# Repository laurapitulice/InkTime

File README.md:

# ⌚ "InkTime smartwatch" - PCB layout in Autodesk Fusion360
InkTime is an e-paper smartwatch designed for month-class battery life, sunlight-readable time-first UX, and essential phone notifications with basic activity
tracking.
Developed in Autodesk Fusion 360, the PCB layout adheres to the precise dimensions and mounting requirements of the wearable chassis, ensuring a seamless fit and optimal component placement.

---

## Hardware Diagram

This is an open-hardware wearable based on the nRF52840 microcontroller.

---

## System Architecture

### 1. Microcontroller (MCU)
- **Chip:** Nordic nRF52840 (Cortex-M4F @ 64MHz)
- **Memory:** 1MB Flash, 256KB RAM
- **Radio:** Bluetooth 5.4 Low Energy with integrated ceramic antenna
- **Oscillators:** 32MHz (operational) and 32.768kHz (sleep mode/RTC)

### 2. Power Management
- **Li-Po Charger:** BQ25180 (I2C control, programmable current)
- **Voltage Regulator:** RT6100 Buck-Boost (stable 3.3V output)
- **Battery Monitoring:** MAX17048 Fuel Gauge (ModelGauge algorithm)
- **Charging Interface:** USB-C with USBLC6-2 ESD protection

### 3. Display (E-Paper)
- **Type:** Electronic Paper Display (EPD)
- **Interface:** SPI + Power Gating Control (PWR_EPD)
- **Drive Circuit:** On-board integrated Boost converter (MBR0530 Diodes, L5 10uH) for VGH/VGL generation

### 4. Sensors and Feedback
- **IMU:** BMA421 (Ultra-low power accelerometer connected via I2C)
- **Haptic:** DRV2605 (Vibration driver with integrated effects library via I2C)
- **Input:** 3 mechanical buttons (UP, ENTER, DOWN) with filtering circuits

### 5. Communication Interfaces (I2C Mapping)
| Component | Function | Interface |
| :--- | :--- | :--- |
| **BMA421** | Motion Sensor | I2C |
| **MAX17048** | Battery Status | I2C |
| **DRV2605** | Vibration Motor | I2C |
| **BQ25180** | Charging | I2C |

---

## nRF52840 Pin Mapping

| Pin nRF52840 | Signal      | Component | Interface |
|-------------|------------|------------|----------|
| P0.00/XL1   | XL1        | Crystal X2 (32.768kHz) | XTAL |
| P0.01/XL2   | XL2        | Crystal X2 (32.768kHz) | XTAL |
| P0.05/AIN3  | EPD_CS     | E-Paper (J1 FPC) | SPI CS |
| P0.06       | SDA        | BMA423, BQ25180, MAX17048, DRV2605 | I2C SDA |
| P0.07       | SCL        | BMA423, BQ25180, MAX17048, DRV2605 | I2C SCL |
| P0.08       | IMU_INT1   | BMA423 | GPIO Input |
| P1.08       | IMU_INT2   | BMA423 | GPIO Input |
| P0.11       | PMIC_INT   | BQ25180 | GPIO Input |
| P0.12       | HAPTIC_EN  | DRV2605 | GPIO |
| VBUS        | VBUS       | USB-C (J4) | Power |
| D-          | D-         | USB-C (J4) / USBLC6 | USB |
| D+          | D+         | USB-C (J4) / USBLC6 | USB |
| P0.13       | SW_UP      | Buton Up | GPIO Input |
| P0.14       | SW_ENT     | Buton Enter | GPIO Input |
| P0.15       | EPD_DC     | E-Paper (J1 FPC) | SPI DC |
| P0.16       | EPD_RST    | E-Paper (J1 FPC) | GPIO |
| P0.17       | EPD_BUSY   | E-Paper (J1 FPC) | GPIO Input |
| P0.18/RESET | RESET      | TC2030-IDC | SWD/GPIO |
| SWDCLK      | SWDCLK     | TC2030-IDC | SWD |
| SWDIO       | SWDIO      | TC2030-IDC | SWD |
| P1.02       | SW_DN      | Buton Down | GPIO Input |
| P0.10/NFC2  | ALERT      | MAX17048 | GPIO Input |
| ANT         | RF         | Antena 2450AT18B100E | RF |
| P0.02/AIN0  | SCK        | E-Paper (J1 FPC) | SPI SCK |
| P0.03/AIN1  | MOSI       | E-Paper (J1 FPC) | SPI MOSI |

---

## Hardware Design & PCB Layout

### 1. Component Placement Strategy
The layout process followed a "mechanical-first" approach to ensure perfect alignment with the enclosure:
* **Mechanical Constraints:** Critical components (USB-C connector, side buttons, and the E-Paper FPC connector) were placed first and **locked** to prevent accidental displacement during the routing process.
* **Logical Grouping:** Components were clustered according to their schematic blocks. ICs were placed centrally to their respective functional areas to minimize signal path lengths.
* **Top-Side Only:** All components are placed exclusively on the **TOP layer** to simplify manufacturing and thermal management.
* **Microcontroller:** The **nRF52840** is positioned relatively in the center of the board to maintain balanced access to all peripheral blocks it commands.
* **User Interface:** Test points and tactile buttons were strategically placed along the board edges for easy access during debugging and final assembly.

### 2. Design Rules & Routing
The board utilizes a **2-layer stack-up** with a focus on signal integrity and power stability:
* **Power & Ground:** 
    * Power traces are maintained at a width of **≥ 0.3 mm**, while signal traces are **≥ 0.15 mm**.
    * **Daisy-chaining** was avoided for power; instead, a **branching topology** was used to prevent ground/power loops.
    * Solid **GND polygon pours** are implemented on both Top and Bottom layers, connected by stitching vias to ensure a low-impedance return path.
* **Decoupling:** 100nF capacitors are placed as close as possible to the power pins of each integrated circuit to filter high-frequency noise.
* **Geometry:** Strictly utilized **45° angles** and smooth miters; 90° bends were eliminated to prevent signal reflections and manufacturing "acid traps."
* **Trace Optimization:** Routes were kept as short as possible. Via usage was minimized, only added when top-layer density required a transition to the bottom layer. Traces were kept away from sensitive areas like the crystal oscillator and inductors.

### 3. RF & EMI Management
Special precautions were taken for the wireless and power sections:
* **Antenna Integrity:** The ceramic antenna is isolated in the top-right corner. A strict **keep-out zone** (no copper, traces, or vias) was maintained around the antenna to prevent signal degradation and interference.
* **Inductor Orientation:** Series inductors (**L2, L3**) are positioned **perpendicularly** (90°) to each other to minimize mutual magnetic coupling and unwanted electromagnetic field amplification.
* **Clean Zones:** No traces were routed underneath inductors, the crystal oscillator, or mounting holes to maintain signal purity.

### 4. Design Rule Check (DRC) & Intentional Exceptions
The design was verified against custom DRC rules. Some errors were manually reviewed and accepted based on specific design requirements:
* **Dimension/Clearance Errors:** The USB-C connector and buttons extend slightly beyond the PCB edge for enclosure alignment. These "Dimension" errors are intentional and neglected.
* **Via-in-Pad:** In extremely dense areas where traditional routing was inaccessible, **0.15 mm micro-vias** were placed within pads to facilitate connectivity.
* **3D Modeling:** 3D models were applied to bulky and critical components for enclosure fit-checks; small passives use standard footprint placeholders.

### 5. Final Verification
* **Clear Silkscreen:** All labels and component designators were cleaned and oriented for high legibility (clear and readable).
* **Connectivity Audit:** A final manual and automated netlist audit was performed to ensure 100% routing completion.
* **Manufacturing Ready:** DRC was cleared of all non-intentional errors, ensuring the board meets professional fabrication capabilities.
  
---

## Debug and Programming
- **SWD:** Programming and debugging via Tag-Connect TC2030 connector
- **USB:** Serial communication and charging

---

## Power Consumption and Battery Life

The device is optimized for ultra-low power operation, leveraging the nRF52840's sleep states and power-gating techniques for high-voltage peripherals.

### Estimated Current Consumption
| Operating Mode | Active Components | Estimated Current |
| :--- | :--- | :--- |
| **Deep Sleep** | MCU (System OFF), Fuel Gauge (Sleep) | ~10 µA |
| **Standby (Idle)** | MCU (System ON), IMU (Low-power) | ~0.8 mA |
| **EPD Refresh** | MCU, EPD Boost Circuit, Display | ~12 mA (peak) |
| **Haptic Alert** | MCU, Haptic Driver + Motor | ~80 mA (peak) |

### Battery Life Estimation
Based on a **200mAh** Li-Po battery:
- **Static Time (Always-on):** Over 1 year (EPD retains the image without power).
- **Typical Usage:** ~10-12 days (with BLE active and 1 refresh/hour).
- **Heavy Usage:** ~4-5 days (frequent haptic notifications and updates).
  
---

## Bill of Materials (BOM)

| Component | Description | Qty | Manufacturer | Part Number | Datasheet |
| :--- | :--- | :--- | :--- | :--- | :--- |
| **Microcontroller** | nRF52840 (AQFN-74) | 1 | Nordic Semiconductor | NRF52840_QF | [Link](https://files.seeedstudio.com/wiki/XIAO-BLE/Nano_BLE_MCU-nRF52840_PS_v1.1.pdf) |
| **Antenna** | 2.45GHz Chip Antenna | 1 | Johanson Technology | 2450AT18B100E | [Link](https://www.johansontechnology.com/datasheets/2450AT18B100.pdf) |
| **Accelerometer** | Triaxial low-g 12bit Sensor | 1 | Bosch Sensortec | BMA423 | [Link](https://watchy.sqfmi.com/assets/files/BST-BMA423-DS000-1509600-950150f51058597a6234dd3eaafbb1f0.pdf) |
| **Battery Charger** | Li-Ion/Polymer Charger IC | 1 | Texas Instruments | BQ25180YBGR | [Link](https://www.ti.com/product/BQ25180) |
| **Haptic Driver** | Driver for ERM/LRA | 1 | Texas Instruments | DRV2605YZFR | [Link](https://www.ti.com/product/DRV2605) |
| **Voltage Regulator** | Buck-Boost DC-DC | 1 | Richtek | RT6160AWSC | [Link](https://www.richtek.com/Products/Switching%20Regulators/Buck-Boost%20Converter/RT6160A) |
| **Fuel Gauge** | 1-Cell/2-Cell Fuel Gauge | 1 | Analog Devices | MAX17048G+T10 | [Link](https://www.analog.com/en/products/max17048.html) |
| **Connector (FPC)** | 0.5mm FPC RA SMT 24Ckt | 1 | Molex | 503480-2400 | [Link](https://www.molex.com/en-us/products/part-detail/5034802400) |
| **Connector (USB)** | USB Type-C 16-pin | 1 | Kinghelm | KH-TYPE-C-16P | [Link](https://jlcpcb.com/api/file/downloadByFileSystemAccessId/8588905154556923904) |
| **ESD Protection** | Low Cap. ESD Protection | 1 | STMicroelectronics | USBLC6-2SC6Y | [Link](https://www.st.com/en/protection-devices/usblc6-2.html) |
| **MOSFET (P)** | P-channel 20V/4.2A | 1 | Diodes Inc. | DMG2305UX-7 | [Link](https://www.lcsc.com/datasheet/C469327.pdf) |
| **MOSFET (N)** | N-channel 30V 1.5A | 1 | Vishay Siliconix | SI1308EDL-T1-GE3 | [Link](https://www.lcsc.com/datasheet/C469327.pdf) |
| **Schottky Diode** | 30V 0.5A Schottky | 3 | ON Semiconductor | MBR0530 | [Link](https://www.onsemi.com/pdf/datasheet/mbr0530t1-d.pdf) |
| **Inductor** | SMD Inductor 0.47µH | 1 | TDK | FTC252012SR47MBCA | [Link](https://jlcpcb.com/partdetail/6763488-FTC252012SR47MBCA/C5832368) |
| **Inductor** | Power Inductor 68uH | 1 | Wurth Electronics | 744043680 | [Link](https://www.we-online.com/en/components/products/WE-TPC) |
| **Switches** | Tactile Switches | 3 | Panasonic | EVP-AKE31A | [Link](https://wmsc.lcsc.com/wmsc/upload/file/pdf/v2/lcsc/2301111010_PANASONIC-EVPAKE31A_C569760.pdf) |
| **Crystals** | 32MHz & 32.768kHz | 2 | Generic/Nordic | X1, X2 | [Link1](https://wmsc.lcsc.com/wmsc/upload/file/pdf/v2/lcsc/2312080231_NDK-NX2016SA-32MHZ-EXS00A-CS11336_C6134317.pdf), [Link2](https://jlcpcb.com/partdetail/SeikoEpson-FC_135_32_7680KAA3/C2650472) |
| **Test Connector** | CABLE ADAPTER 6 POS | 1 | Tag Connect | TC2030-IDC | [Link](https://www.tag-connect.com/wp-content/uploads/bsk-pdf-manager/2019/12/TC2030-IDC-Datasheet-Rev-B.pdf) |

** The design and implementation of this PCB were based on the technical guidelines and reference designs provided by [OCW](https://ocw.cs.pub.ro/courses/tsc/proiect2026).

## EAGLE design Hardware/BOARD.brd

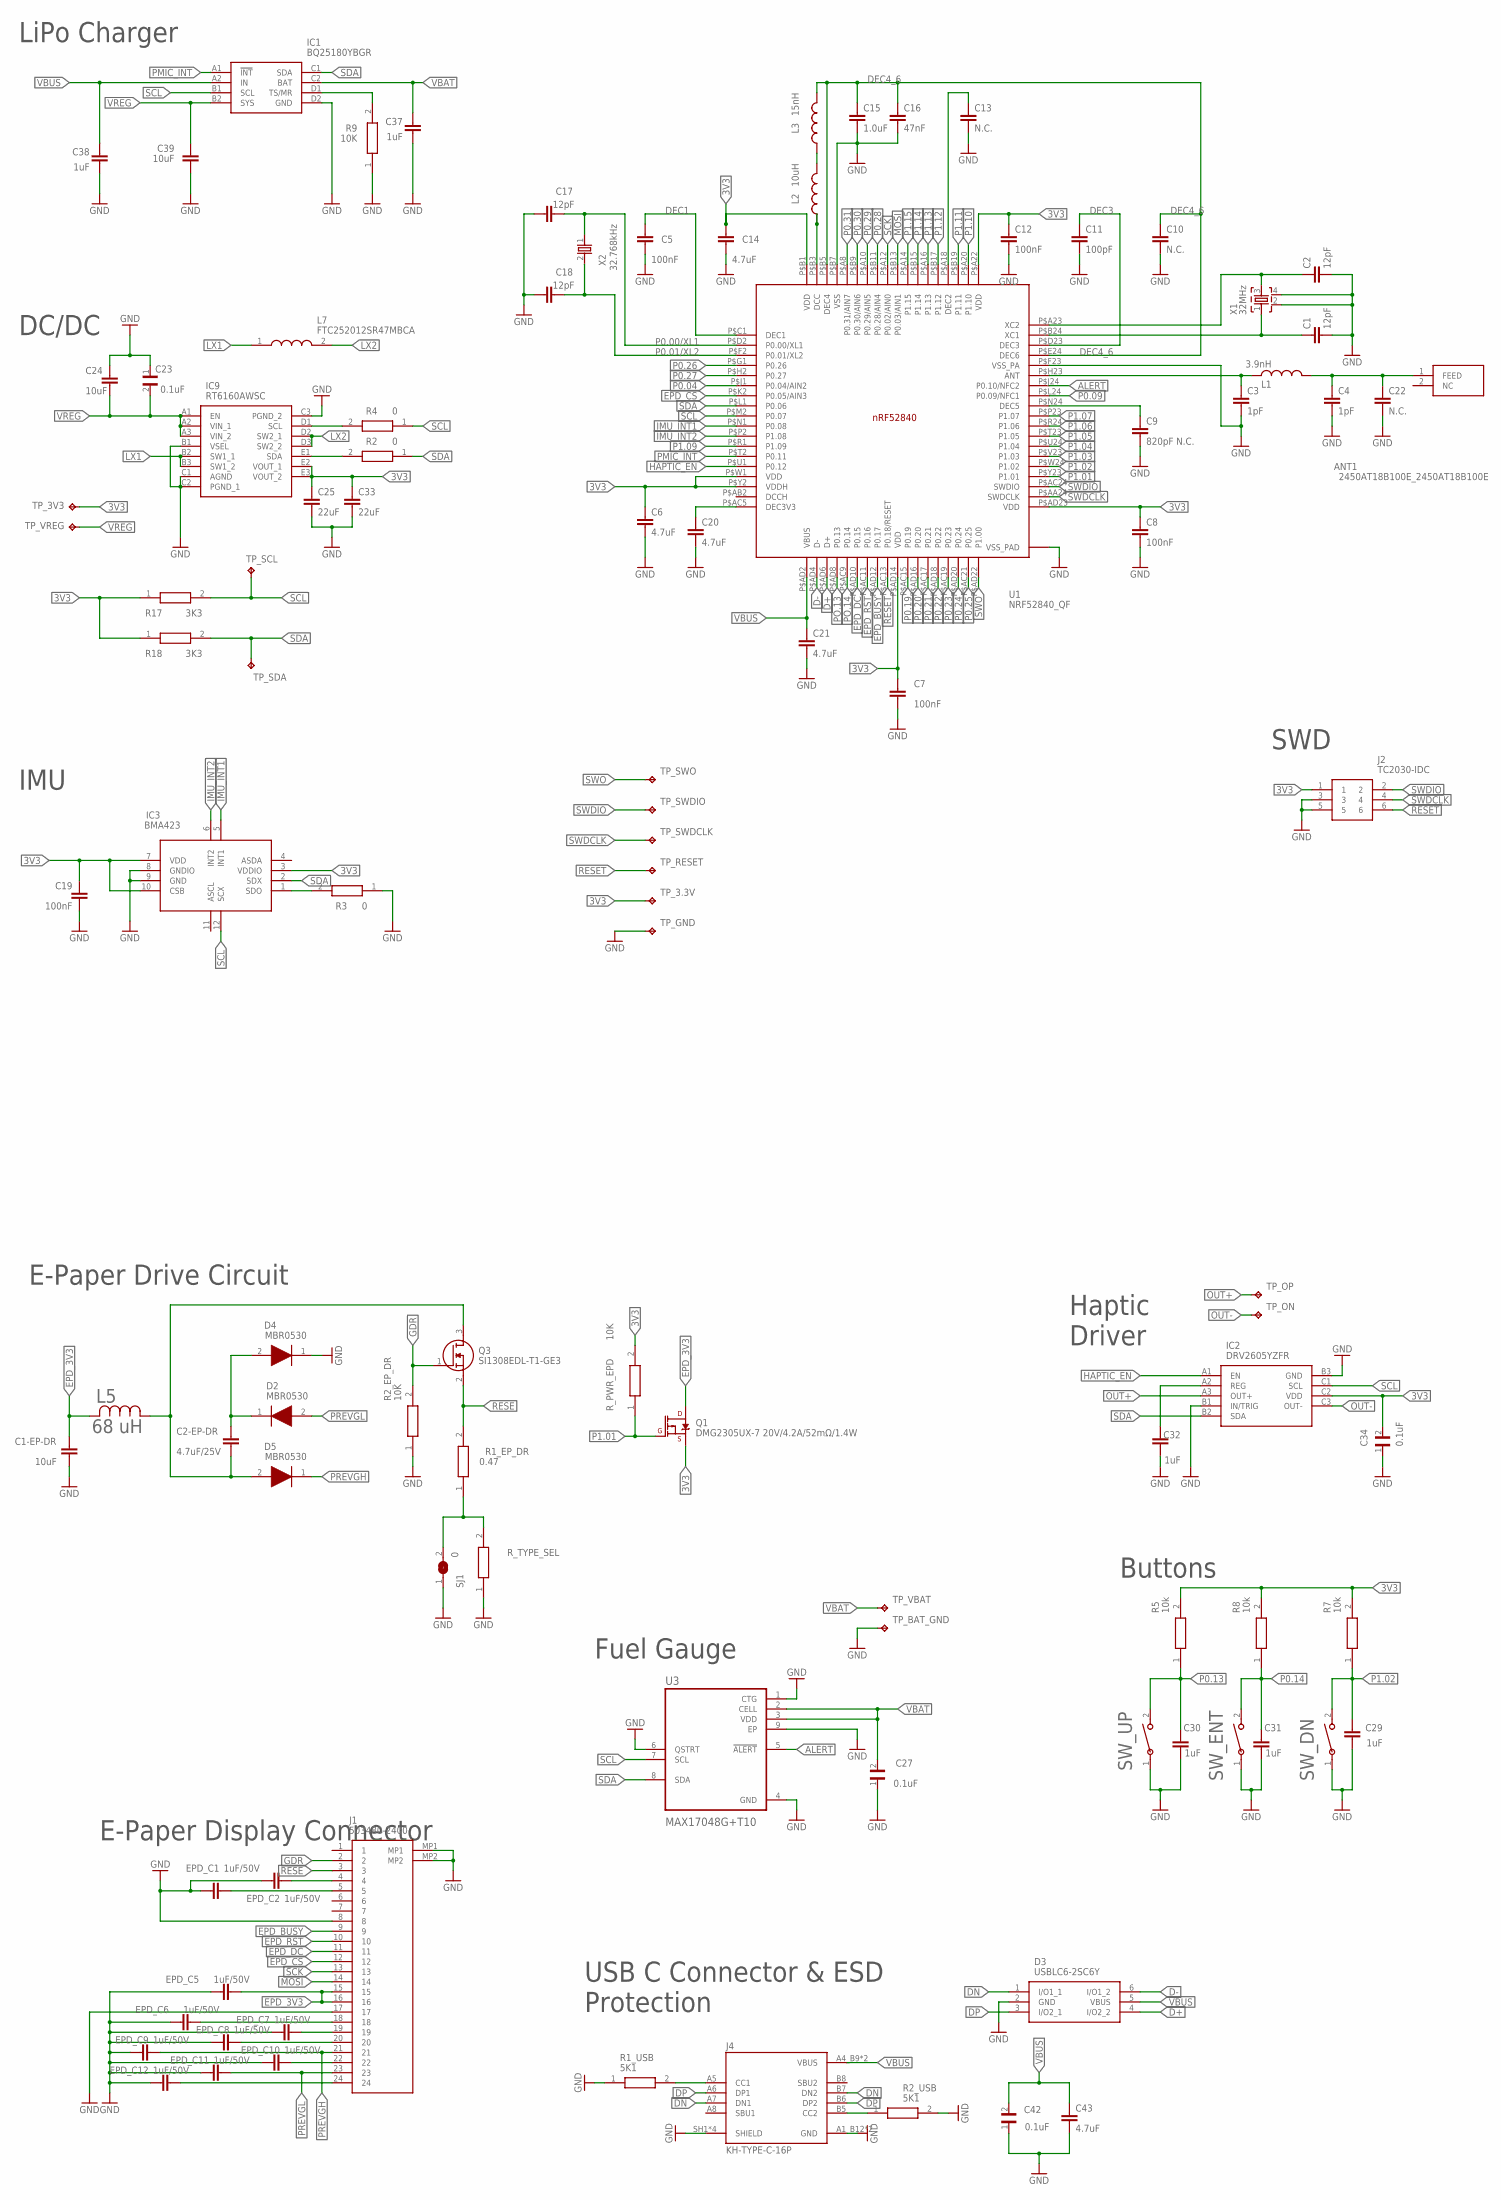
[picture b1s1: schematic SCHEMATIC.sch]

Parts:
ANT1: 2450AT18B100E_2450AT18B100E; 2450AT18B100E_ANTC3216X140N
C1, C2, C17, C18: 12pF; NORDIC_NRF_3_RESC0201_L
C1-EP-DR, C24: 10uF; PERFECT_0402_0402
C2-EP-DR: 4.7uF/25V; PERFECT_0402_0402
C3, C4: 1pF; NORDIC_NRF_3_RESC0201_L
C5, C7, C8, C12, C19: 100nF; NORDIC_NRF_3_RESC0201_L
C6, C14, C20, C21, C43: 4.7uF; PERFECT_0402_0402
C9: 820pF N.C.; NORDIC_NRF_3_RESC0201_L
C10, C13, C22: N.C.; NORDIC_NRF_3_RESC0201_L
C11: 100pF; NORDIC_NRF_3_RESC0201_L
C15: 1.0uF; PERFECT_0402_0402
C16: 47nF; NORDIC_NRF_3_RESC0201_L
C23: 0.1uF; GRM011R60J152KE01L_1_0201
C25, C33: 22uF; PERFECT_0402_0402
C27, C34, C42: 0.1uF; GRM011R60J152KE01L_2_CAPC0201X13N
C29, C30, C31, C32, C37, C38: 1uF; NORDIC_NRF_3_RESC0402_L
C39: 10uF; NORDIC_NRF_3_RESC0402_L
D2, D4, D5: MBR0530; ESP32_C6_LIBRARY_5_SOD3716X135N
D3: USBLC6-2SC6Y; ESP32_C6_LIBRARY_3_SOT95P280X145-6N
EPD_C1, EPD_C2, EPD_C5, EPD_C6, EPD_C7, EPD_C8, EPD_C9, EPD_C10, EPD_C11, EPD_C12: 1uF/50V; PERFECT_0402_0402
IC1: BQ25180YBGR; BQ25180YBGR_BGA8C40P2X4_100X155X50
IC2: DRV2605YZFR; DRV2605YZFR_BGA9C50P3X3_144X144X62
IC3: BMA423; BMA423_BMA423
IC9: RT6160AWSC; RT6160AWSC_BGA15C40P3X5_140X230X60
J1: 503480-2400; 503480-2400_5034802400
J2: TC2030-IDC; TC2030-IDC_TC2030IDC
J4: KH-TYPE-C-16P; KH-TYPE-C-16P_KINGHELM_KH-TYPE-C-16P
L1: 3.9nH; NORDIC_NRF_2_RESC0402_L
L2: 10uH; NORDIC_NRF_2_RESC0402_L
L3: 15nH; NORDIC_NRF_2_RESC0402_L
L5: 68 uH; ESP32_C6_LIBRARY_2_IND_4828-WE-TPC_WRE
L7: FTC252012SR47MBCA; MLP2016SR47MT0S1_INDC2016X100N
Q1: DMG2305UX-7 20V/4.2A/52mΩ/1.4W; ESP32_C6_LIBRARY_4_ESP32_C6_LIBRARY_4_ESP32_C6_LIBRARY_4_ES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
Q3: SI1308EDL-T1-GE3; ESP32_C6_LIBRARY_6_SOT65P210X110-3N
R1_EP_DR: 0.47; ERA-1AEB3401C_0201
R1_USB, R2_USB: 5K1; CPF0201D7K68C1_0201
R2, R4: 0; ERA-1AEB3401C_0201
R2_EP_DR, R9: 10K; ERA-1AEB3401C_0201
R3: 0; CPF0201D7K68C1_0201
R5, R7, R8: 10k; CPF0201D7K68C1_0201
R17, R18: 3K3; ERA-1AEB3401C_0201
R_PWR_EPD: 10K; CPF0201D7K68C1_0201
R_TYPE_SEL: 2.2; ERA-1AEB3401C_0201
SJ1: 0; ESP32_C6_LIBRARY_7_JUMPER_SJ
SW_DN: 2025-10-22_07-23-44_LIBRARY_EVP-AKE31ASW_EVP-AKE3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; 2025-10-22_07-23-44_LIBRARY_SW_EVP-AKE31A_PAN
SW_ENT: 2025-10-22_07-23-44_LIBRARY_EVP-AKE31ASW_EVP-AKE3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; 2025-10-22_07-23-44_LIBRARY_SW_EVP-AKE31A_PAN
SW_UP: 2025-10-22_07-23-44_LIBRARY_EVP-AKE31ASW_EVP-AKE3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; 2025-10-22_07-23-44_LIBRARY_SW_EVP-AKE31A_PAN
TP_3.3V, TP_3V3: HECTOR_WATCH_1_TPTP20R; HECTOR_WATCH_1_TP20R
TP_BAT_GND: HECTOR_WATCH_1_TPTP20R; HECTOR_WATCH_1_TP20R
TP_GND: HECTOR_WATCH_1_TPTP20R; HECTOR_WATCH_1_TP20R
TP_ON: HECTOR_WATCH_1_TPTP20R; HECTOR_WATCH_1_TP20R
TP_OP: HECTOR_WATCH_1_TPTP20R; HECTOR_WATCH_1_TP20R
TP_RESET: HECTOR_WATCH_1_TPTP20R; HECTOR_WATCH_1_TP20R
TP_SCL: HECTOR_WATCH_1_TPTP20R; HECTOR_WATCH_1_TP20R
TP_SDA: HECTOR_WATCH_1_TPTP20R; HECTOR_WATCH_1_TP20R
TP_SWDCLK: HECTOR_WATCH_1_TPTP20R; HECTOR_WATCH_1_TP20R
TP_SWDIO: HECTOR_WATCH_1_TPTP20R; HECTOR_WATCH_1_TP20R
TP_SWO: HECTOR_WATCH_1_TPTP20R; HECTOR_WATCH_1_TP20R
TP_VBAT: HECTOR_WATCH_1_TPTP20R; HECTOR_WATCH_1_TP20R
TP_VREG: HECTOR_WATCH_1_TPTP20R; HECTOR_WATCH_1_TP20R
U1: NRF52840_QF; NORDIC_NRF_4_AQFN50P700X700X85_HS-74N
U3: MAX17048G+T10; ESP32_C6_LIBRARY_SON50P200X200X80-9N
X1: 32MHz; NORDIC_NRF_BT-XTAL_2016_N
X2: 32.768kHz; NORDIC_NRF_1_XTAL_3215_N

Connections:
3V3: C6.1, C7.1, C8.1, C12.1, C14.1, C19.1, C25.1, C33.1, C34.2, IC2.C2 (VDD), IC3.3 (VDDIO), IC3.7 (VDD), IC3.10 (CSB), IC9.E2 (VOUT_1), IC9.E3 (VOUT_2), J2.1, Q1.2 (S), R5.2, R7.2, R8.2, R17.1, R18.1, R_PWR_EPD.2, TP_3.3V.TP, TP_3V3.TP, U1.P$A22 (VDD), U1.P$AD14 (VDD), U1.P$AD23 (VDD), U1.P$B1 (VDD), U1.P$W1 (VDD), U1.P$Y2 (VDDH)
ALERT: U1.P$J24 (P0.10/NFC2), U3.5 (!ALERT)
D+: D3.4 (I/O2_2), U1.P$AD6 (D+)
D-: D3.6 (I/O1_2), U1.P$AD4 (D-)
DEC1: C5.1, U1.P$C1 (DEC1)
DEC3: C11.1, U1.P$D23 (DEC3)
DEC4_6: C10.1, C15.1, C16.1, L3.2, U1.P$B5 (DEC4), U1.P$E24 (DEC6)
DN: D3.1 (I/O1_1), J4.A7 (DN1), J4.B7 (DN2)
DP: D3.3 (I/O2_1), J4.A6 (DP1), J4.B6 (DP2)
EPD_3V3: C1-EP-DR.1, EPD_C5.2, J1.15, J1.16, L5.2, Q1.3 (D)
EPD_BUSY: J1.9, U1.P$AD12 (P0.17)
EPD_CS: J1.12, U1.P$K2 (P0.05/AIN3)
EPD_DC: J1.11, U1.P$AD10 (P0.15)
EPD_RST: J1.10, U1.P$AC11 (P0.16)
GDR: J1.2, Q3.1 (G), R2_EP_DR.2
GND: C1.2, C1-EP-DR.2, C2.2, C3.2, C4.2, C5.2, C6.2, C7.2, C8.2, C9.2, C10.2, C11.2, C12.2, C13.2, C14.2, C15.2, C16.2, C17.1, C18.1, C19.2, C20.2, C21.2, C22.2, C23.1, C24.1, C25.2, C27.1, C29.1, C30.1, C31.1, C32.1, C33.2, C34.1, C37.1, C38.1, C39.1, C42.1, C43.2, D3.2 (GND), D4.1 (K), EPD_C1.1, EPD_C2.1, EPD_C5.1, EPD_C6.1, EPD_C7.1, EPD_C8.1, EPD_C9.1, EPD_C10.1, EPD_C11.1, EPD_C12.1, IC1.D2 (GND), IC2.B1 (IN/TRIG), IC2.B3 (GND), IC3.8 (GNDIO), IC3.9 (GND), IC9.B1 (VSEL), IC9.C1 (AGND), IC9.C2 (PGND_1), IC9.C3 (PGND_2), J1.8, J1.17, J1.MP1, J1.MP2, J2.3, J2.5, J4.A1_B12 (GND), J4.A12_B1 (GND), J4.SH1 (SHIELD), J4.SH2 (SHIELD), J4.SH3 (SHIELD), J4.SH4 (SHIELD), R1_USB.1, R2_EP_DR.1, R2_USB.2, R3.1, R9.1, R_TYPE_SEL.1, SJ1.1, SW_DN.1, SW_ENT.1, SW_UP.1, TP_BAT_GND.TP, TP_GND.TP, U1.P$74 (VSS_PAD), U1.P$75 (VSS_PAD), U1.P$76 (VSS_PAD), U1.P$77 (VSS_PAD), U1.P$78 (VSS_PAD), U1.P$79 (VSS_PAD), U1.P$80 (VSS_PAD), U1.P$81 (VSS_PAD), U1.P$82 (VSS_PAD), U1.P$83 (VSS_PAD), U1.P$84 (VSS_PAD), U1.P$85 (VSS_PAD), U1.P$86 (VSS_PAD), U1.P$87 (VSS_PAD), U1.P$88 (VSS_PAD), U1.P$89 (VSS_PAD), U1.P$90 (VSS_PAD), U1.P$B7 (VSS), U1.P$F23 (VSS_PA), U3.1 (CTG), U3.4 (GND), U3.6 (QSTRT), U3.9 (EP), X1.2, X1.4
HAPTIC_EN: IC2.A1 (EN), U1.P$U1 (P0.12)
IMU_INT1: IC3.5 (INT1), U1.P$N1 (P0.08)
IMU_INT2: IC3.6 (INT2), U1.P$P2 (P1.08)
LX1: IC9.B2 (SW1_1), IC9.B3 (SW1_2), L7.1
LX2: IC9.D2 (SW2_1), IC9.D3 (SW2_2), L7.2
MOSI: J1.14, U1.P$B13 (P0.03/AIN1)
unnamed: ANT1.1 (FEED), C4.1, C22.1, L1.2
unnamed: IC9.D1 (SCL), R4.2
unnamed: IC1.D1 (TS/MR), R9.2
unnamed: C2.1, U1.P$A23 (XC2), X1.3
unnamed: IC9.E1 (SDA), R2.2
unnamed: J4.A5 (CC1), R1_USB.2
unnamed: L2.2, L3.1
unnamed: IC3.1 (SDO), R3.2
unnamed: C1.1, U1.P$B24 (XC1), X1.1
unnamed: C3.1, L1.1, U1.P$H23 (ANT)
unnamed: C32.2, IC2.A2 (REG)
unnamed: C2-EP-DR.1, D2.1 (K), D4.2 (A)
unnamed: C9.1, U1.P$N24 (DEC5)
unnamed: R1_EP_DR.1, R_TYPE_SEL.2, SJ1.2
unnamed: C2-EP-DR.2, D5.2 (A), L5.1, Q3.3 (D)
unnamed: EPD_C2.2, J1.4
unnamed: EPD_C1.2, J1.5
unnamed: C20.1, U1.P$AC5 (DEC3V3)
unnamed: L2.1, U1.P$B3 (DCC)
unnamed: J4.B5 (CC2), R2_USB.1
unnamed: EPD_C6.2, J1.18
unnamed: EPD_C7.2, J1.19
unnamed: EPD_C8.2, J1.20
unnamed: EPD_C10.2, J1.22
unnamed: C13.1, U1.P$A18 (DEC2)
unnamed: EPD_C12.2, J1.24
OUT+: IC2.A3 (OUT+), TP_OP.TP
OUT-: IC2.C3 (OUT-), TP_ON.TP
P0.00/XL1: C17.2, U1.P$D2 (P0.00/XL1), X2.1
P0.01/XL2: C18.2, U1.P$F2 (P0.01/XL2), X2.2
P0.04: U1.P$J1 (P0.04/AIN2)
P0.09: U1.P$L24 (P0.09/NFC1)
P0.13: C30.2, R5.1, SW_UP.2
P0.14: C31.2, R8.1, SW_ENT.2
P0.19: U1.P$AC15 (P0.19)
P0.20: U1.P$AD16 (P0.20)
P0.21: U1.P$AC17 (P0.21)
P0.22: U1.P$AD18 (P0.22)
P0.23: U1.P$AC19 (P0.23)
P0.24: U1.P$AD20 (P0.24)
P0.25: U1.P$AC21 (P0.25)
P0.26: U1.P$G1 (P0.26)
P0.27: U1.P$H2 (P0.27)
P0.28: U1.P$B11 (P0.28/AIN4)
P0.29: U1.P$A10 (P0.29/AIN5)
P0.30: U1.P$B9 (P0.30/AIN6)
P0.31: U1.P$A8 (P0.31/AIN7)
P1.01: Q1.1 (G), R_PWR_EPD.1, U1.P$Y23 (P1.01)
P1.02: C29.2, R7.1, SW_DN.2, U1.P$W24 (P1.02)
P1.03: U1.P$V23 (P1.03)
P1.04: U1.P$U24 (P1.04)
P1.05: U1.P$T23 (P1.05)
P1.06: U1.P$R24 (P1.06)
P1.07: U1.P$P23 (P1.07)
P1.09: U1.P$R1 (P1.09)
P1.10: U1.P$A20 (P1.10)
P1.11: U1.P$B19 (P1.11)
P1.12: U1.P$B17 (P1.12)
P1.13: U1.P$A16 (P1.13)
P1.14: U1.P$B15 (P1.14)
P1.15: U1.P$A14 (P1.15)
PMIC_INT: IC1.A1 (!INT), U1.P$T2 (P0.11)
PO.13: U1.P$AD8 (P0.13)
PO.14: U1.P$AC9 (P0.14)
PREVGH: D5.1 (K), EPD_C9.2, J1.21
PREVGL: D2.2 (A), EPD_C11.2, J1.23
RESE: J1.3, Q3.2 (S), R1_EP_DR.2
RESET: J2.6, TP_RESET.TP, U1.P$AC13 (P0.18/RESET)
SCK: J1.13, U1.P$A12 (P0.02/AIN0)
SCL: IC1.B1 (SCL), IC2.C1 (SCL), IC3.12 (SCX), R4.1, R17.2, TP_SCL.TP, U1.P$M2 (P0.07), U3.7 (SCL)
SDA: IC1.C1 (SDA), IC2.B2 (SDA), IC3.2 (SDX), R2.1, R18.2, TP_SDA.TP, U1.P$L1 (P0.06), U3.8 (SDA)
SWDCLK: J2.4, TP_SWDCLK.TP, U1.P$AA24 (SWDCLK)
SWDIO: J2.2, TP_SWDIO.TP, U1.P$AC24 (SWDIO)
SWO: TP_SWO.TP, U1.P$AD22 (P1.00)
VBAT: C27.2, C37.2, IC1.C2 (BAT), TP_VBAT.TP, U3.2 (CELL), U3.3 (VDD)
VBUS: C21.1, C38.2, C42.2, C43.1, D3.5 (VBUS), IC1.A2 (IN), J4.A4_B9 (VBUS), J4.A9_B4 (VBUS), U1.P$AD2 (VBUS)
VREG: C23.2, C24.2, C39.2, IC1.B2 (SYS), IC9.A1 (EN), IC9.A2 (VIN_1), IC9.A3 (VIN_2), TP_VREG.TP

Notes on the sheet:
LiPo Charger
DC/DC
IMU
SWD
E-Paper Drive Circuit
E-Paper Display Connector
Fuel Gauge
Haptic Driver
Buttons
USB C Connector & ESD Protection

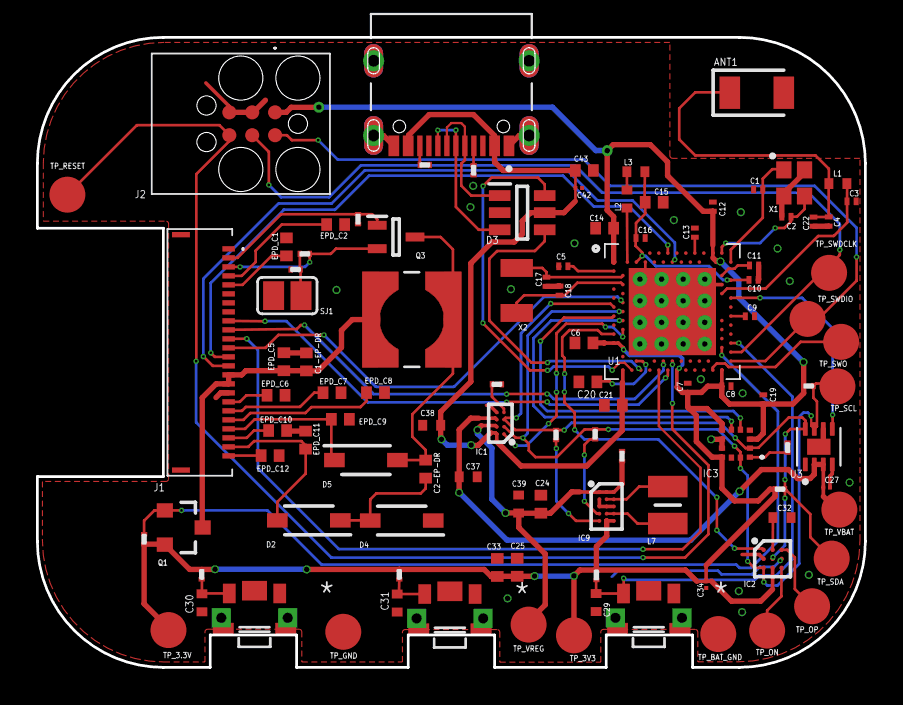
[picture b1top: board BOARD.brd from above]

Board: 2 copper layers, 46.0 x 35.0 mm, 105 parts (0 on the bottom side), 70 nets.

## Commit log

2026-05-02 Rename Screenshot 2026-05-02 202107.png to TOP_LAYER_2D.png
2026-05-02 Rename Screenshot 2026-05-02 202259.png to BOTTOM_LAYER_2D.png
2026-05-02 Rename diagram.png to block_diagram.png
2026-05-02 Rename Screenshot 2026-05-02 203003.png to PCB_2D.png
2026-05-02 Rename image_2026-05-02_203625408.png to PCB_3D_side_view.png
2026-05-02 Rename BOTTOM_LAYER_2D.png to PCB_2D_bottom_layer.png
2026-05-02 Rename TOP_LAYER_2D.png to PCB_2D_top_layer.png
2026-05-02 Rename PCB_2D.png to PCB_2D_full.png
2026-05-02 Rename PCB_2D_full.png to PCB_2D.png
2026-05-02 Rename image_2026-05-02_204040226.png to PCB_3D_top_view.png
2026-05-02 Rename image_2026-05-02_204213431.png to PCB_3D_bottom_view.png
2026-05-02 Rename image_2026-05-02_210034415.png to smartwatch_3D.png
2026-05-02 Rename BOARD.csv to BOM.csv
2026-05-02 Rename drill_1_64.xln to Drill.xln

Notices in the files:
parts and their libraries:
COPYRIGHT: Copyright (C) 2024 Ultra Librarian. All rights reserved.
COPYRIGHT: Copyright (C) 2025 Ultra Librarian. All rights reserved.
